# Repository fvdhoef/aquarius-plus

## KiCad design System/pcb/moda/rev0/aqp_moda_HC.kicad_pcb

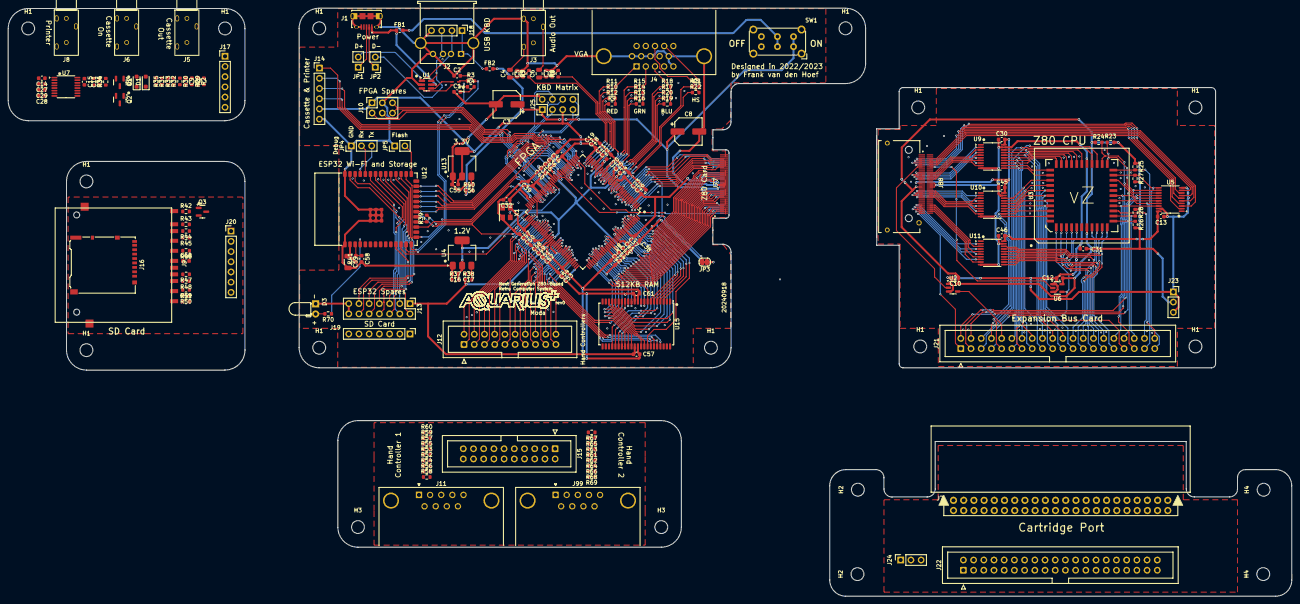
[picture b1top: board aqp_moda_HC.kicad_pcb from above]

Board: 2 copper layers, 319.5 x 146.3 mm, 207 parts (0 on the bottom side), 250 nets.

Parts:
C1, C2: DNP; C_0603_1608Metric
C3, C8: 100uF; CP_Elec_6.3x7.7
C4, C6: 10uF; C_0805_2012Metric
C5, C7, C9, C10, C12, C13, C14, C18, C20, C21, C22, C24, C25, C26, C27, C28, C29, C30, C31, C32, C33, C34, C37, C38, C39, C40, C41, C43, C44, C45, C46, C47, C48, C51, C52, C54, C57, C58, C61: 100nF; C_0603_1608Metric
C11, C15, C16, C17, C19, C23, C35, C36, C42, C49, C50, C53, C55, C56, C60: 4.7uF; C_0603_1608Metric
C59: 22uF; C_1206_3216Metric
D1, D2: 1N4148WS; D_SOD-323_HandSoldering
D3: SD act.; LED_D3.0mm_Horizontal_O1.27mm_Z2.0mm
FB1, FB2: 220; L_0603_1608Metric
H1, H1#2, H1#3, H1#4, H1#5, H1#6, H1#7, H1#8, H1#9, H1#10, H1#11, H1#12, H2, H2#2, H3, H3#2, H4, H4#2: MountingHole; MountingHole_3.2mm_M3
J1: Power in; AMPHENOL_10118194-0001LF
J2: ESP USB Host; USB_A_Molex_67643_Horizontal
J3: Audio out; C2939180
J4: VGA; ICD15S13E4GV00LF
J5: Cassette out; C2939180
J6: Cassette in; C2939180
J7: Expansion port; CR22A-44D-2.54DSA(70)
J8: Printer; C2939180
J9: TF-03A
J10: Conn_02x03_Top_Bottom; PinSocket_2x03_P2.54mm_Vertical
J11, J99: Hand Controller; DSUB-9_Male_Horizontal_P2.77x2.84mm_EdgePinOffset9.90mm_Hou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
J12, J15: Conn_02x10_Odd_Even; IDC-Header_2x10_P2.54mm_Vertical
J13: ESP32 spare; PinHeader_2x07_P2.54mm_Vertical
J14, J17: Conn_01x06_Socket; PinHeader_1x06_P2.54mm_Vertical
J16: Micro_SD_Card_Det1; microSD_HC_Hirose_DM3AT-SF-PEJM5
J18: Conn_01x04; PinHeader_1x04_P2.54mm_Vertical
J19, J20: Conn_01x07; PinHeader_1x07_P2.54mm_Vertical
J21, J22: Conn_02x20_Top_Bottom; IDC-Header_2x20_P2.54mm_Vertical
J23, J24: Conn_01x03; PinSocket_1x03_P2.54mm_Vertical
J25: KBD Matrix; PinHeader_2x04_P2.54mm_Vertical
J77: MEC5-030-01-X-RA-W1-XX-EDGE; SAMTEC_MEC5-030-01-X-RA-W1-XX-EDGE
J88: MEC5-030-01-X-RA-W1-XX-SOCKET; SAMTEC_MEC5-030-01-X-RA-W1-XX
JP1, JP2: Pin Header; PinHeader_1x02_P2.54mm_Vertical
JP3: vZ80 Enabled; SolderJumper-2_P1.3mm_Bridged_RoundedPad1.0x1.5mm
JP4: DBG; PinHeader_1x03_P2.54mm_Vertical
JP5: Bootloader; PinHeader_1x02_P2.54mm_Vertical
L1: USB Choke; WE-CNSW_08058
Q1, Q2: BC847C; SOT-23
Q3: 2N7002; SOT-23
R1, R41, R42, R43, R45, R47, R50, R51: 10k; R_0603_1608Metric
R2, R37, R44, R46, R48, R49, R52, R53, R54, R55, R56, R57, R58, R59, R60, R61, R62, R63, R64, R65, R66, R67, R68, R69: 100; R_0603_1608Metric
R3, R4, R38, R40: 0; R_0603_1608Metric
R5, R6: 150; R_0603_1608Metric
R7, R8: 330; R_0603_1608Metric
R9, R16, R19: 4300; R_0603_1608Metric
R10, R14, R17: 1070; R_0603_1608Metric
R11, R15, R18: 536; R_0603_1608Metric
R12, R13, R20: 2150; R_0603_1608Metric
R21, R22: 820; R_0603_1608Metric
R23, R24, R25, R26, R27, R28: 1k; R_0603_1608Metric
R29: 82; R_0603_1608Metric
R30, R31: 47k; R_0603_1608Metric
R32, R39, R70: 220; R_0603_1608Metric
R33: 220k; R_0603_1608Metric
R34, R35: 4.7k; R_0603_1608Metric
R36: 2.2k; R_0603_1608Metric
SW1: SW_DPDT_x2; SW_E-Switch_EG2219_DPDT_Angled
U1: IP4234CZ6; SC-74-6_1.55x2.9mm_P0.95mm
U2, U6: SN74AHCT1G125DBVR; SOT-23-5
U3: PLCC-44 SMD Socket; PLCC-44_SMD-Socket
U4: LD1117S12; SOT-223-3_TabPin2
U5, U9, U10, U11: SN74CB3T3245PWR; TSSOP-20_4.4x6.5mm_P0.65mm
U7: MAX3221ECPWR; TSSOP-16_4.4x5mm_P0.65mm
U8: XC6SLX9-2TQG144C; TQFP-144_20x20mm_P0.5mm
U12: ESP32-S3-WROOM-1-N4R2; ESP32-S2-SOLO-N4R2
U13: LDL1117S33R; SOT-223-3_TabPin2
U15: IS61C5128AL-10TLI; TSOP-II-44_10.16x18.41mm_P0.8mm
X1: SX3M14.31818M20F30TNN; Oscillator_SMD_SeikoEpson_SG8002CE-4Pin_3.2x2.5mm

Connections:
+1V2: C16.1, C22.1, C25.1, C33.1, C35.1, C41.1, C49.1, C51.1, R37.2, U4.2 (VO), U8.19 (VCCINT), U8.28 (VCCINT), U8.52 (VCCINT), U8.89 (VCCINT), U8.128 (VCCINT)
+3V3: C13.1, C15.1, C18.1, C19.1, C20.1, C21.1, C23.1, C24.1, C26.1, C30.1, C32.1, C34.1, C36.1, C37.1, C38.1, C39.1, C40.1, C42.1, C43.1, C44.1, C45.1, C46.1, C47.1, C48.1, C50.1, C52.1, C53.1, C54.1, C55.1, C57.1, C59.1, C60.1, C61.1, J9.4 (VDD), J10.1, J13.1, J14.5, J16.4 (VDD), J17.5, J25.5, J77.29, J88.29, R31.2, R33.2, R34.2, R35.2, R38.1, R41.1, R42.2, R43.2, R45.2, R47.2, R50.2, R51.2, U5.20 (VCC), U7.12 (FORCEON), U7.15 (VCC), U7.16 (~FORCEOFF), U8.4 (VCCO_3), U8.18 (VCCO_3), U8.20 (VCCAUX), U8.31 (VCCO_3), U8.36 (VCCAUX), U8.42 (VCCO_2), U8.53 (VCCAUX), U8.60 (B2_IO_M1), U8.63 (VCCO_2), U8.69 (B2_IO_M0), U8.76 (VCCO_1), U8.86 (VCCO_1), U8.90 (VCCAUX), U8.103 (VCCO_1), U8.122 (VCCO_0), U8.125 (VCCO_0), U8.129 (VCCAUX), U8.135 (VCCO_0), U9.20 (VCC), U10.20 (VCC), U11.20 (VCC), U12.2 (3V3), U13.2 (VO), U15.11 (VDD), U15.33 (VDD), X1.4 (VCC)
+5V: C3.1, C8.1, C10.1, C12.1, C31.1, FB2.2, J7.25, J23.2, J24.2, J25.1, J77.33, J88.33, R23.1, R24.1, R25.1, R26.1, R27.1, R28.1, R40.1, SW1.1 (A), SW1.4 (A), U2.5 (VCC), U3.13 (+5V), U6.5 (VCC)
/USB_D+: J1.3 (D+), JP1.1 (A)
/USB_D-: J1.2 (D-), JP2.1 (A)
A0: J7.23, J21.22, J22.22, U3.34 (A0), U9.18 (B1)
A1: J7.21, J21.20, J22.20, U3.35 (A1), U9.17 (B2)
A2: J7.19, J21.18, J22.18, U3.36 (A2), U9.16 (B3)
A3: J7.17, J21.16, J22.16, U3.37 (A3), U9.15 (B4)
A4: J7.15, J21.14, J22.14, U3.38 (A4), U9.14 (B5)
A5: J7.13, J21.12, J22.12, U3.39 (A5), U9.13 (B6)
A6: J7.12, J21.11, J22.11, U3.40 (A6), U9.12 (B7)
A7: J7.14, J21.13, J22.13, U3.41 (A7), U9.11 (B8)
A8: J7.16, J21.15, J22.15, U3.42 (A8), U10.18 (B1)
A9: J7.18, J21.17, J22.17, U3.43 (A9), U10.17 (B2)
A10: J7.20, J21.19, J22.19, U3.44 (A10), U10.16 (B3)
A11: J7.22, J21.21, J22.21, U3.1 (A11), U10.15 (B4)
A12: J7.24, J21.23, J22.23, U3.2 (A12), U10.14 (B5)
A13: J7.36, J21.33, J22.33, U3.3 (A13), U10.13 (B6)
A14: J7.10, J21.9, J22.9, U3.4 (A14), U10.12 (B7)
A15: J7.9, J21.8, J22.8, U3.5 (A15), U10.11 (B8)
AUDIO_L: R7.1, U8.35 (B3_IO)
AUDIO_R: R8.1, U8.34 (B3_IO_VREF)
BA14: U8.101 (B1_IO), U15.30 (A14)
BA15: U8.102 (B1_IO), U15.38 (A15)
BA16: U8.100 (B1_IO), U15.39 (A16)
BA17: U8.99 (B1_IO), U15.40 (A17)
BA18: U8.104 (B1_IO_VREF), U15.41 (A18)
BUSACK#: J7.42, J21.39, J22.39, R27.2, U3.27 (~BUSACK), U5.11 (B8)
BUSREQ#: J7.4, J21.3, J22.3, R23.2, U3.29 (~BUSREQ), U5.12 (B7)
CART_CE#: J7.11, J21.10, J22.10, U2.4
CASSETTE_IN: J14.2, J17.2, Q2.3 (C), R35.1, U8.40 (B2_IO)
CASSETTE_OUT: J7.2, J14.1, J17.1, J21.1, J22.1, J77.59, J88.59, R1.1, U8.38 (B2_IO)
D0: J7.26, J21.24, J22.24, U3.16 (D0), U11.18 (B1)
D1: J7.27, J21.25, J22.25, U3.17 (D1), U11.17 (B2)
D2: J7.28, J21.26, J22.26, U3.14 (D2), U11.16 (B3)
D3: J7.29, J21.27, J22.27, U3.9 (D3), U11.15 (B4)
D4: J7.30, J21.28, J22.28, U3.8 (D4), U11.14 (B5)
D5: J7.31, J21.29, J22.29, U3.10 (D5), U11.13 (B6)
D6: J7.32, J21.30, J22.30, U3.11 (D6), U11.12 (B7)
D7: J7.33, J21.31, J22.31, U3.15 (D7), U11.11 (B8)
ESP_CTS: U8.44 (B2_IO), U12.24 (IO47)
ESP_EXP0: J13.2, U12.39 (IO1)
ESP_EXP1: J13.3, U12.38 (IO2)
ESP_EXP2: J13.4, U12.35 (IO42)
ESP_EXP3: J13.5, U12.34 (IO41)
ESP_EXP4: J13.6, U12.33 (IO40)
ESP_EXP5: J13.7, U12.32 (IO39)
ESP_EXP6: J13.8, U12.31 (IO38)
ESP_EXP7: J13.9, U12.30 (IO37)
ESP_EXP8: J13.10, U12.29 (IO36)
ESP_EXP9: J13.11, U12.28 (IO35)
ESP_EXP10: J13.12, U12.11 (IO18)
ESP_NOTIFY: U8.48 (B2_IO), U12.20 (IO12)
ESP_RTS: U8.46 (B2_IO), U12.22 (IO14)
ESP_RX: U8.45 (B2_IO), U12.23 (IO21)
ESP_TX: U8.47 (B2_IO_VREF), U12.21 (IO13)
ESP_USB_D+: C1.2, R4.2, U12.14 (IO20/USB_DP)
ESP_USB_D-: C2.2, R3.2, U12.13 (IO19/USB_DM)
FPGA_A0: J77.19, J88.19, U8.143 (B0_IO_VREF), U9.2 (A1), U15.3 (A0)
FPGA_A1: J77.20, J88.20, U8.142 (B0_IO), U9.3 (A2), U15.4 (A1)
FPGA_A2: J77.21, J88.21, U8.141 (B0_IO), U9.4 (A3), U15.5 (A2)
FPGA_A3: J77.22, J88.22, U8.140 (B0_IO), U9.5 (A4), U15.6 (A3)
FPGA_A4: J77.23, J88.23, U8.139 (B0_IO), U9.6 (A5), U15.7 (A4)
FPGA_A5: J77.24, J88.24, U8.138 (B0_IO), U9.7 (A6), U15.16 (A5)
FPGA_A6: J77.25, J88.25, U8.137 (B0_IO), U9.8 (A7), U15.17 (A6)
FPGA_A7: J77.26, J88.26, U8.134 (B0_IO_GCLK19), U9.9 (A8), U15.18 (A7)
FPGA_A8: J77.37, J88.37, U8.133 (B0_IO_GCLK18), U10.2 (A1), U15.19 (A8)
FPGA_A9: J77.38, J88.38, U8.132 (B0_IO_GCLK17), U10.3 (A2), U15.20 (A9)
FPGA_A10: J77.39, J88.39, U8.131 (B0_IO_GCLK16), U10.4 (A3), U15.26 (A10)
FPGA_A11: J77.40, J88.40, U8.127 (B0_IO_GCLK15), U10.5 (A4), U15.27 (A11)
FPGA_A12: J77.41, J88.41, U8.126 (B0_IO_GCLK14), U10.6 (A5), U15.28 (A12)
FPGA_A13: J77.42, J88.42, U8.124 (B0_IO_GCLK13), U10.7 (A6), U15.29 (A13)
FPGA_A14: J77.43, J88.43, U8.123 (B0_IO_GCLK12), U10.8 (A7)
FPGA_A15: J77.44, J88.44, U8.121 (B0_IO), U10.9 (A8)
FPGA_BUSACK#: J77.12, J88.12, U5.9 (A8), U8.5 (B3_IO)
FPGA_BUSREQ#: J77.11, J88.11, U5.8 (A7), U8.6 (B3_IO)
FPGA_CART_CE#: J77.13, J88.13, U2.2, U8.2 (B3_IO)
FPGA_D0: J77.51, J88.51, U8.120 (B0_IO_VREF), U11.2 (A1), U15.9 (I/O0)
FPGA_D1: J77.52, J88.52, U8.119 (B0_IO), U11.3 (A2), U15.10 (I/O1)
FPGA_D2: J77.53, J88.53, U8.118 (B0_IO), U11.4 (A3), U15.13 (I/O2)
FPGA_D3: J77.54, J88.54, U8.117 (B0_IO), U11.5 (A4), U15.14 (I/O3)
FPGA_D4: J77.55, J88.55, U8.116 (B0_IO), U11.6 (A5), U15.31 (I/O4)
FPGA_D5: J77.56, J88.56, U8.115 (B0_IO), U11.7 (A6), U15.32 (I/O5)
FPGA_D6: J77.57, J88.57, U8.114 (B0_IO), U11.8 (A7), U15.35 (I/O6)
FPGA_D7: J77.58, J88.58, U8.112 (B0_IO), U11.9 (A8), U15.36 (I/O7)
FPGA_DONE: U8.71 (DONE), U12.12 (IO8)
FPGA_EXP5: J10.2, U8.58 (B2_IO)
FPGA_EXP6: J10.4, U8.57 (B2_IO)
FPGA_EXP7: J10.5, U8.56 (B2_IO_GCLK1)
FPGA_EXP8: J10.6, U8.51 (B2_IO_GCLK31)
FPGA_INT#: J77.09, J88.09, U5.6 (A5), U8.8 (B3_IO)
FPGA_IORQ#: J77.06, J88.06, U5.3 (A2), U8.11 (B3_IO)
FPGA_MREQ#: J77.05, J88.05, U5.2 (A1), U8.12 (B3_IO)
FPGA_PHI: J77.14, J88.14, U6.2, U8.1 (B3_IO)
FPGA_PROG#: U8.37 (PROG_B), U12.25 (IO48)
FPGA_RD#: J77.07, J88.07, U5.4 (A3), U8.10 (B3_IO), U15.37 (~OE)
FPGA_RESET#: J77.10, J88.10, U5.7 (A6), U8.7 (B3_IO)
FPGA_WR#: J77.08, J88.08, U5.5 (A4), U8.9 (B3_IO)
GND: C1.1, C2.1, C3.2, C5.2, C7.2, C8.2, C10.2, C12.2, C13.2, C15.2, C16.2, C17.2, C18.2, C19.2, C20.2, C21.2, C22.2, C23.2, C24.2, C25.2, C26.2, C27.2, C28.2, C30.2, C31.2, C32.2, C33.2, C34.2, C35.2, C36.2, C37.2, C38.2, C39.2, C40.2, C41.2, C42.2, C43.2, C44.2, C45.2, C46.2, C47.2, C48.2, C49.2, C50.2, C51.2, C52.2, C53.2, C54.2, C55.2, C56.2, C57.2, C58.2, C59.2, C60.2, C61.2, D1.2 (A), D2.2 (A), D3.1 (K), J1.5 (GND), J1.6 (Shield), J2.4 (GND), J2.5 (Shield), J3.S, J4.0, J4.5, J4.6, J4.7, J4.8, J4.10, J5.S, J6.S, J7.34, J7.44, J8.S, J9.3 (VSS), J9.6 (VSS), J9.12 (SHELL1), J9.13 (SHELL2), J10.3, J11.0 (PAD), J13.13, J13.14, J14.6, J16.6 (VSS), J16.10 (SHIELD), J17.6, J18.4, J23.1, J23.3, J24.1, J24.3, J25.2, J77.30, J77.32, J77.34, J88.30, J88.32, J88.34, J99.0 (PAD), JP3.1 (A), JP4.1, JP5.1 (A), Q2.2 (E), Q3.2 (S), R2.1, R5.1, R6.1, R29.1, R30.1, R32.1, R37.1, U1.2 (VN), U2.1, U2.3 (GND), U3.33 (GND), U4.1 (GND), U5.10 (GND), U5.19 (~OE), U6.1, U6.3 (GND), U7.1 (~EN), U7.14 (GND), U8.3 (GND), U8.13 (GND), U8.25 (GND), U8.49 (GND), U8.54 (GND), U8.68 (GND), U8.73 (SUSPEND), U8.77 (GND), U8.91 (GND), U8.96 (GND), U8.108 (GND), U8.113 (GND), U8.130 (GND), U8.136 (GND), U9.10 (GND), U9.19 (~OE), U10.10 (GND), U10.19 (~OE), U11.10 (GND), U11.19 (~OE), U12.1 (GND), U12.40 (GND), U12.41 (EPAD), U13.1 (GND), U15.12 (GND), U15.34 (GND), X1.2 (GND)
HALT#: J7.41, J21.38, J22.38, U3.20 (~HALT)
HC1_D00: J12.2, U8.75 (B1_IO_AWAKE)
HC1_D01: J12.3, U8.79 (B1_IO)
HC1_D02: J12.4, U8.81 (B1_IO)
HC1_D03: J12.5, U8.83 (B1_IO)
HC1_D04: J12.6, U8.84 (B1_IO_GCLK4)
HC1_D05: J12.7, U8.82 (B1_IO)
HC1_D06: J12.8, U8.80 (B1_IO)
HC1_D07: J12.9, U8.78 (B1_IO)
HC1_D08: J12.1, U8.67 (B2_IO)
HC2_D00: J12.19, U8.87 (B1_IO_GCLK6)
HC2_D01: J12.18, U8.92 (B1_IO_GCLK8)
HC2_D02: J12.17, U8.94 (B1_IO_GCLK10)
HC2_D03: J12.16, U8.97 (B1_IO)
HC2_D04: J12.15, U8.98 (B1_IO)
HC2_D05: J12.14, U8.95 (B1_IO_GCLK11)
HC2_D06: J12.13, U8.93 (B1_IO_GCLK9)
HC2_D07: J12.12, U8.88 (B1_IO_GCLK7)
HC2_D08: J12.20, U8.85 (B1_IO_GCLK5)
INT#: J7.3, J21.2, J22.2, R26.2, U3.18 (~INT), U5.14 (B5)
IORQ#: J7.43, J21.40, J22.40, U3.22 (~IORQ), U5.17 (B2)
KBD-DOut: J25.8, U8.59 (B2_IO)
KBD-FirstCol: J25.6, U8.66 (B2_IO)
KBD-Load#: J25.7, U8.62 (B2_IO)
KBD-NextCol: J25.3, U8.64 (B2_IO)
KBD-ShCLK: J25.4, U8.61 (B2_IO)
M1#: J7.6, J21.5, J22.5, U3.31 (~M1)
MREQ#: J7.38, J21.35, J22.35, U3.21 (~MREQ), U5.18 (B1)
NMI#: J7.39, J21.36, J22.36, R28.2, U3.19 (~NMI)
unnamed: C4.1, C5.1, R5.2, R7.2
unnamed: C4.2, J3.T
unnamed: C6.1, C7.1, R6.2, R8.2
unnamed: C6.2, J3.R
unnamed: C9.1, J6.T, R29.2
unnamed: C11.2, R36.1
unnamed: C9.2, D1.1 (K), Q1.1 (B), R30.2, R33.1
unnamed: D2.1 (K), Q2.1 (B), R31.1, R36.2
unnamed: D3.2 (A), R70.2
unnamed: FB1.1, J1.1 (VBUS), U1.5 (VP)
unnamed: J4.1, R9.2, R10.2, R11.2, R12.2
unnamed: J4.2, R13.2, R14.2, R15.2, R16.2
unnamed: J4.3, R17.2, R18.2, R19.2, R20.2
unnamed: J4.13, R22.2
unnamed: J4.14, R21.2
unnamed: J5.T, R1.2, R2.2
unnamed: J9.11 (WRITE_PROTECT), Q3.1 (G), R42.1
unnamed: J11.1, R60.1
unnamed: J11.2, R58.1
unnamed: J11.3, R56.1
unnamed: J11.4, R54.1
unnamed: J11.5, R52.1
unnamed: J11.6, R59.1
unnamed: J11.7, R57.1
unnamed: J11.8, R55.1
unnamed: J11.9, R53.1
unnamed: J9.5 (CLK), J16.5 (CLK), R46.2
unnamed: J9.2 (CMD), J16.3 (CMD), R48.2
unnamed: J9.7 (DAT0), J16.7 (DAT0), R44.2
unnamed: J9.8 (DAT1), J16.8 (DAT1), R43.1
unnamed: J9.9 (DAT2), J16.1 (DAT2), R51.1
unnamed: J9.1 (CD/DAT3), J16.2 (DAT3/CD), R49.2
unnamed: FB2.1, J2.1 (VBUS), J18.1
unnamed: J2.2 (D-), J18.2, JP1.2 (B), U1.1
unnamed: J2.3 (D+), J18.3, JP2.2 (B), U1.6
unnamed: J99.1, R69.1
unnamed: J99.2, R67.1
unnamed: J99.3, R65.1
unnamed: J99.4, R63.1
unnamed: J99.5, R61.1
unnamed: J99.6, R68.1
unnamed: J99.7, R66.1
unnamed: J99.8, R64.1
unnamed: J99.9, R62.1
unnamed: JP4.2, U12.36 (IO44/RXD0)
unnamed: JP4.3, U12.37 (IO43/TXD0)
unnamed: JP5.2 (B), U12.27 (IO0)
unnamed: L1.1, R4.1
unnamed: L1.2, U1.3
unnamed: L1.3, U1.4
unnamed: L1.4, R3.1
unnamed: C11.1, Q1.3 (C), R34.1
unnamed: Q1.2 (E), R32.2
unnamed: C17.1, R38.2, U4.3 (VI)
unnamed: C14.1, U7.2 (C1+)
unnamed: C14.2, U7.4 (C1-)
unnamed: C29.1, U7.5 (C2+)
unnamed: C29.2, U7.6 (C2-)
unnamed: J8.T, U7.13 (DOUT)
unnamed: J8.R, U7.8 (RIN)
unnamed: C27.1, U7.3 (V+)
unnamed: C28.1, U7.7 (V-)
unnamed: R39.2, U8.70 (B2_IO_CCLK)
unnamed: C58.1, R41.2, U12.3 (EN)
unnamed: C56.1, R40.2, U13.3 (VI)
PHI: J7.8, J21.7, J22.7, U3.7 (CLK), U6.4
PRINTER_IN: J14.4, J17.4, U7.9 (ROUT), U8.41 (B2_IO)
PRINTER_OUT: J14.3, J17.3, U7.11 (DIN), U8.43 (B2_IO)
RAM_CE#: U8.111 (B0_IO), U15.8 (~CE)
RAM_WE#: U8.105 (B1_IO), U15.15 (~WE)
RD#: J7.35, J21.32, J22.32, U3.23 (~RD), U5.16 (B3)
RESET#: J7.5, J21.4, J22.4, R24.2, U3.30 (~RESET), U5.13 (B6)
RFSH#: J7.7, J21.6, J22.6, U3.32 (~RFSH)
SD_ACTIVITY: R70.1, U12.4 (IO4)
SD_CD: J9.10 (CARD_DETECT), J16.9 (DET), U12.6 (IO6)
SD_MISO: R44.1, R45.1, U12.7 (IO7)
SD_MOSI: R47.1, R48.1, U12.9 (IO16)
SD_SCK: R46.1, U12.8 (IO15)
SD_SSEL#: R49.1, R50.1, U12.10 (IO17)
SD_WP#: Q3.3 (D), U12.5 (IO5)
SPI_CS#: U8.39 (B2_IO_INIT_B), U12.15 (IO3)
SPI_MISO: U8.74 (B2_IO_DOUT), U12.19 (IO11)
SPI_MOSI: U8.65 (B2_IO_DIN), U12.17 (IO9)
SPI_SCLK: R39.1, U12.18 (IO10)
SUB_HC1_D00: J15.2, R59.2
SUB_HC1_D01: J15.3, R57.2
SUB_HC1_D02: J15.4, R55.2
SUB_HC1_D03: J15.5, R53.2
SUB_HC1_D04: J15.6, R52.2
SUB_HC1_D05: J15.7, R54.2
SUB_HC1_D06: J15.8, R56.2
SUB_HC1_D07: J15.9, R58.2
SUB_HC1_D08: J15.1, R60.2
SUB_HC2_D00: J15.19, R68.2
SUB_HC2_D01: J15.18, R66.2
SUB_HC2_D02: J15.17, R64.2
SUB_HC2_D03: J15.16, R62.2
SUB_HC2_D04: J15.15, R61.2
SUB_HC2_D06: J15.13, R65.2
SUB_HC2_D07: J15.12, R67.2
SUB_HC2_D08: J15.20, R69.2
SUB_HC2_DO5: J15.14, R63.2
SYSCLK: U8.55 (B2_IO_GCLK0), X1.3 (OUT)
VBUS: FB1.2, SW1.2 (B), SW1.5 (B)
VGA_B0: R19.1, U8.16 (B3_IO_GCLK22)
VGA_B1: R20.1, U8.17 (B3_IO_GCLK23)
VGA_B2: R17.1, U8.21 (B3_IO_GCLK24)
VGA_B3: R18.1, U8.22 (B3_IO_GCLK25)
VGA_G0: R16.1, U8.23 (B3_IO_GCLK26)
VGA_G1: R13.1, U8.24 (B3_IO_GCLK27)
VGA_G2: R14.1, U8.26 (B3_IO)
VGA_G3: R15.1, U8.27 (B3_IO)
VGA_HSYNC: R22.1, U8.14 (B3_IO_GCLK20)
VGA_R0: R9.1, U8.29 (B3_IO)
VGA_R1: R12.1, U8.30 (B3_IO)
VGA_R2: R10.1, U8.32 (B3_IO)
VGA_R3: R11.1, U8.33 (B3_IO)
VGA_VSYNC: R21.1, U8.15 (B3_IO_GCLK21)
WAIT#: J7.40, J21.37, J22.37, R25.2, U3.28 (~WAIT)
WR#: J7.37, J21.34, J22.34, U3.26 (~WR), U5.15 (B4)
vZ80 Sense: JP3.2 (B), U8.50 (B2_IO_GCLK30)

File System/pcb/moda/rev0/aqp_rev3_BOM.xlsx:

Comment | Designator | Footprint | JLCPCB Part #
100nF | C5,C7,C9,C10,C12,C13,C14,C18,C20,C21,C22,C24,C25,C26,C27,C28,C29,C30,C31,C32,C3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 | Capacitor_SMD:C_0603_1608Metric | C14663
100 | R2,R37,R44,R46,R48,R49,R52,R53,R54,R55,R56,R57,R58,R59,R60,R61,R62,R63,R64,R65,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 | Resistor_SMD:R_0603_1608Metric | C22775
4.7uF | C11,C15,C16,C17,C19,C23,C35,C36,C42,C49,C50,C53,C55,C56,C60 | Capacitor_SMD:C_0603_1608Metric | C19666
10k | R1,R41,R42,R43,R45,R47,R50,R51 | Resistor_SMD:R_0603_1608Metric | C25804
1k | R23,R24,R25,R26,R27,R28 | Resistor_SMD:R_0603_1608Metric | C21190
SN74CB3T3245PWR | U5,U9,U10,U11 | Package_SO:TSSOP-20_4.4x6.5mm_P0.65mm | C15298
0 | R3,R4,R38,R40 | Resistor_SMD:R_0603_1608Metric | C2784885
-- mixed values -- | J3,J5,J6,J8 | aquarius-plus:C2939180 | C2939180
220 | R32,R39,R70 | Resistor_SMD:R_0603_1608Metric | C22962
2150 | R12,R13,R20 | Resistor_SMD:R_0603_1608Metric | C170518
536 | R11,R15,R18 | Resistor_SMD:R_0603_1608Metric | C227956
1070 | R10,R14,R17 | Resistor_SMD:R_0603_1608Metric | C137783
4300 | R9,R16,R19 | Resistor_SMD:R_0603_1608Metric | C23159
-- mixed values -- | JP1,JP2,JP5 | Connector_PinHeader_2.54mm:PinHeader_1x02_P2.54mm_Vertical | C5116481
-- mixed values -- | U4,U13 | Package_TO_SOT_SMD:SOT-223-3_TabPin2 | C155612
SN74AHCT1G125DBVR | U2,U6 | Package_TO_SOT_SMD:SOT-23-5 | C7484
4.7k | R34,R35 | Resistor_SMD:R_0603_1608Metric | C23162
47k | R30,R31 | Resistor_SMD:R_0603_1608Metric | C25819
820 | R21,R22 | Resistor_SMD:R_0603_1608Metric | C23253
330 | R7,R8 | Resistor_SMD:R_0603_1608Metric | C23138
150 | R5,R6 | Resistor_SMD:R_0603_1608Metric | C22808
BC847C | Q1,Q2 | Package_TO_SOT_SMD:SOT-23 | C181141
Hand Controller | J11,J12 | Connector_Dsub:DSUB-9_Male_Horizontal_P2.77x2.84mm_EdgePinOffset9.90mm_Housed_M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 | C305940
220 | FB1,FB2 | Inductor_SMD:L_0603_1608Metric | C2661695
1N4148WS | D1,D2 | Diode_SMD:D_SOD-323_HandSoldering | C2128
10uF | C4,C6 | Capacitor_SMD:C_0805_2012Metric | C15850
100uF | C3,C8 | Capacitor_SMD:CP_Elec_6.3x7.7 | C264047
SX3M14.31818M20F30TNN | X1 | Oscillator:Oscillator_SMD_SeikoEpson_SG8002CE-4Pin_3.2x2.5mm | C2901565
IS61C5128AS-25QLI | U14 | Package_SO:SSOP-32_11.305x20.495mm_P1.27mm | C443416
ESP32-S3-WROOM-1-N4R2 | U12 | aquarius-plus:ESP32-S2-SOLO-N4R2 | C2913203
XC6SLX9-2TQG144C | U8 | Package_QFP:TQFP-144_20x20mm_P0.5mm | C27408
MAX3221ECPWR | U7 | Package_SO:TSSOP-16_4.4x5mm_P0.65mm | C350553
PLCC-44 SMD Socket | U3 | Package_LCC:PLCC-44_SMD-Socket | C2828044
IP4234CZ6 | U1 | Package_TO_SOT_SMD:SC-74-6_1.55x2.9mm_P0.95mm | C455086
SW_DPDT_x2 | SW1 | Button_Switch_THT:SW_E-Switch_EG2219_DPDT_Angled | C3664594
2.2k | R36 | Resistor_SMD:R_0603_1608Metric | C4190
220k | R33 | Resistor_SMD:R_0603_1608Metric | C22961
82 | R29 | Resistor_SMD:R_0603_1608Metric | C23255
2N7002 | Q3 | Package_TO_SOT_SMD:SOT-23 | C8545
USB Choke | L1 | Inductor_SMD:L_CommonMode_Wurth_WE-CNSW-1206 | C2649327
TF-03A | J9 | aquarius-plus:TF-03A | C693842
Expansion port | J7 | aquarius-plus:CR22A-44D-2.54DSA(70) | C7431259
VGA | J4 | aquarius-plus:ICD15S13E4GV00LF | C138387
ESP USB Host | J2 | Connector_USB:USB_A_Molex_67643_Horizontal | C2798029
Power in | J1 | aquarius-plus:AMPHENOL_10118194-0001LF | C132563
SD act. | D3 | LED_THT:LED_D3.0mm_Horizontal_O1.27mm_Z2.0mm | C330760
22uF | C59 | Capacitor_SMD:C_1206_3216Metric | C12891

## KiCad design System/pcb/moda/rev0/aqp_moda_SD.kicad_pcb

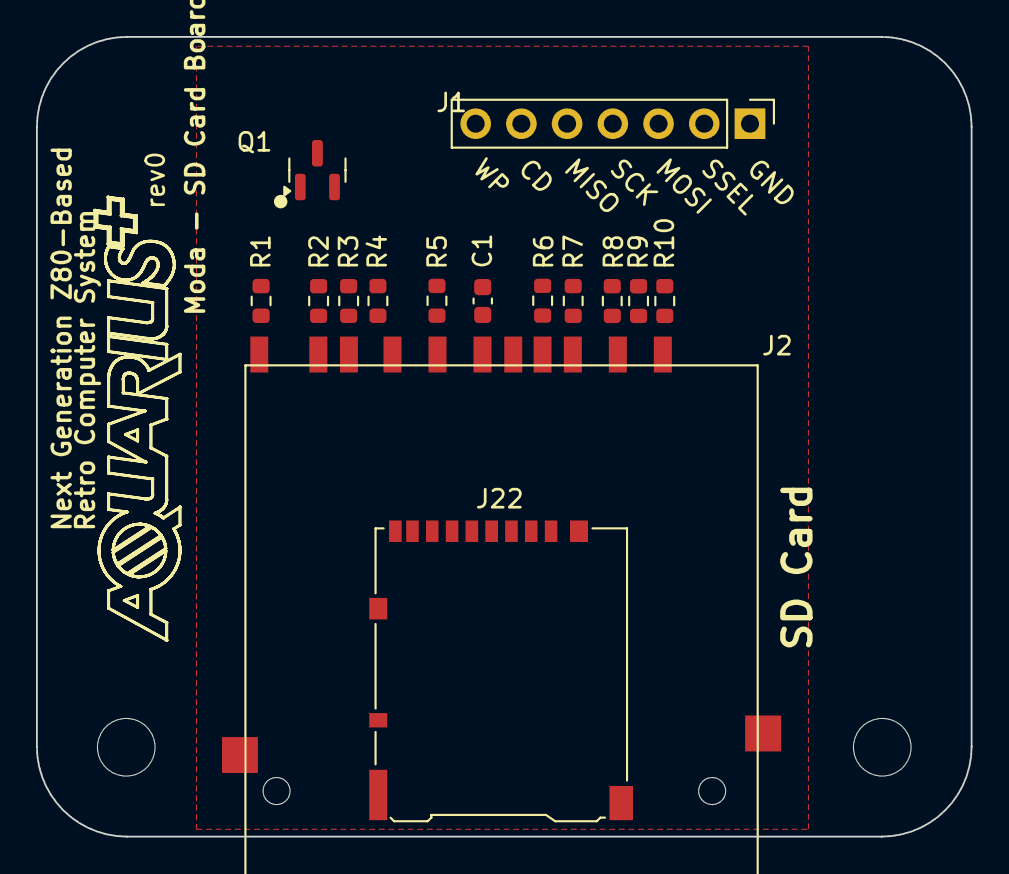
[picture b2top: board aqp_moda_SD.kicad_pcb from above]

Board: 2 copper layers, 51.9 x 44.4 mm, 17 parts (0 on the bottom side), 13 nets, no tracks yet.

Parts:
C1: 4.7uF; C_0603_1608Metric
H1, H2: MountingHole; MountingHole_3.2mm_M3
J1: Conn_01x07; PinHeader_1x07_P2.54mm_Vertical
J2: TF-03A
J22: Micro_SD_Card_Det1; microSD_HC_Hirose_DM3AT-SF-PEJM5
Q1: 2N7002; SOT-23
R1, R2, R4, R6, R9, R10: 10k; R_0603_1608Metric
R3, R5, R7, R8: 100; R_0603_1608Metric

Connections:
+3V3: C1.1, J2.4 (VDD), J22.4 (VDD), R1.2, R2.2, R4.2, R6.2, R9.2, R10.2
GND: C1.2, J2.3 (VSS), J2.6 (VSS), J2.12 (SHELL1), J2.13 (SHELL2), J22.6 (VSS), J22.10 (SHIELD), Q1.2 (S)
unnamed: J2.11 (WRITE_PROTECT), Q1.1 (G), R1.1
unnamed: J2.5 (CLK), J22.5 (CLK), R5.2
unnamed: J2.2 (CMD), J22.3 (CMD), R7.2
unnamed: J2.7 (DAT0), J22.7 (DAT0), R3.2
unnamed: J2.8 (DAT1), J22.8 (DAT1), R2.1
unnamed: J2.9 (DAT2), J22.1 (DAT2), R9.1
unnamed: J2.1 (CD/DAT3), J22.2 (DAT3/CD), R8.2
SD_CD: J2.10 (CARD_DETECT), J22.9 (DET)
SD_MISO: R3.1, R4.1
SD_MOSI: R6.1, R7.1
SD_SSEL#: R8.1, R10.1
